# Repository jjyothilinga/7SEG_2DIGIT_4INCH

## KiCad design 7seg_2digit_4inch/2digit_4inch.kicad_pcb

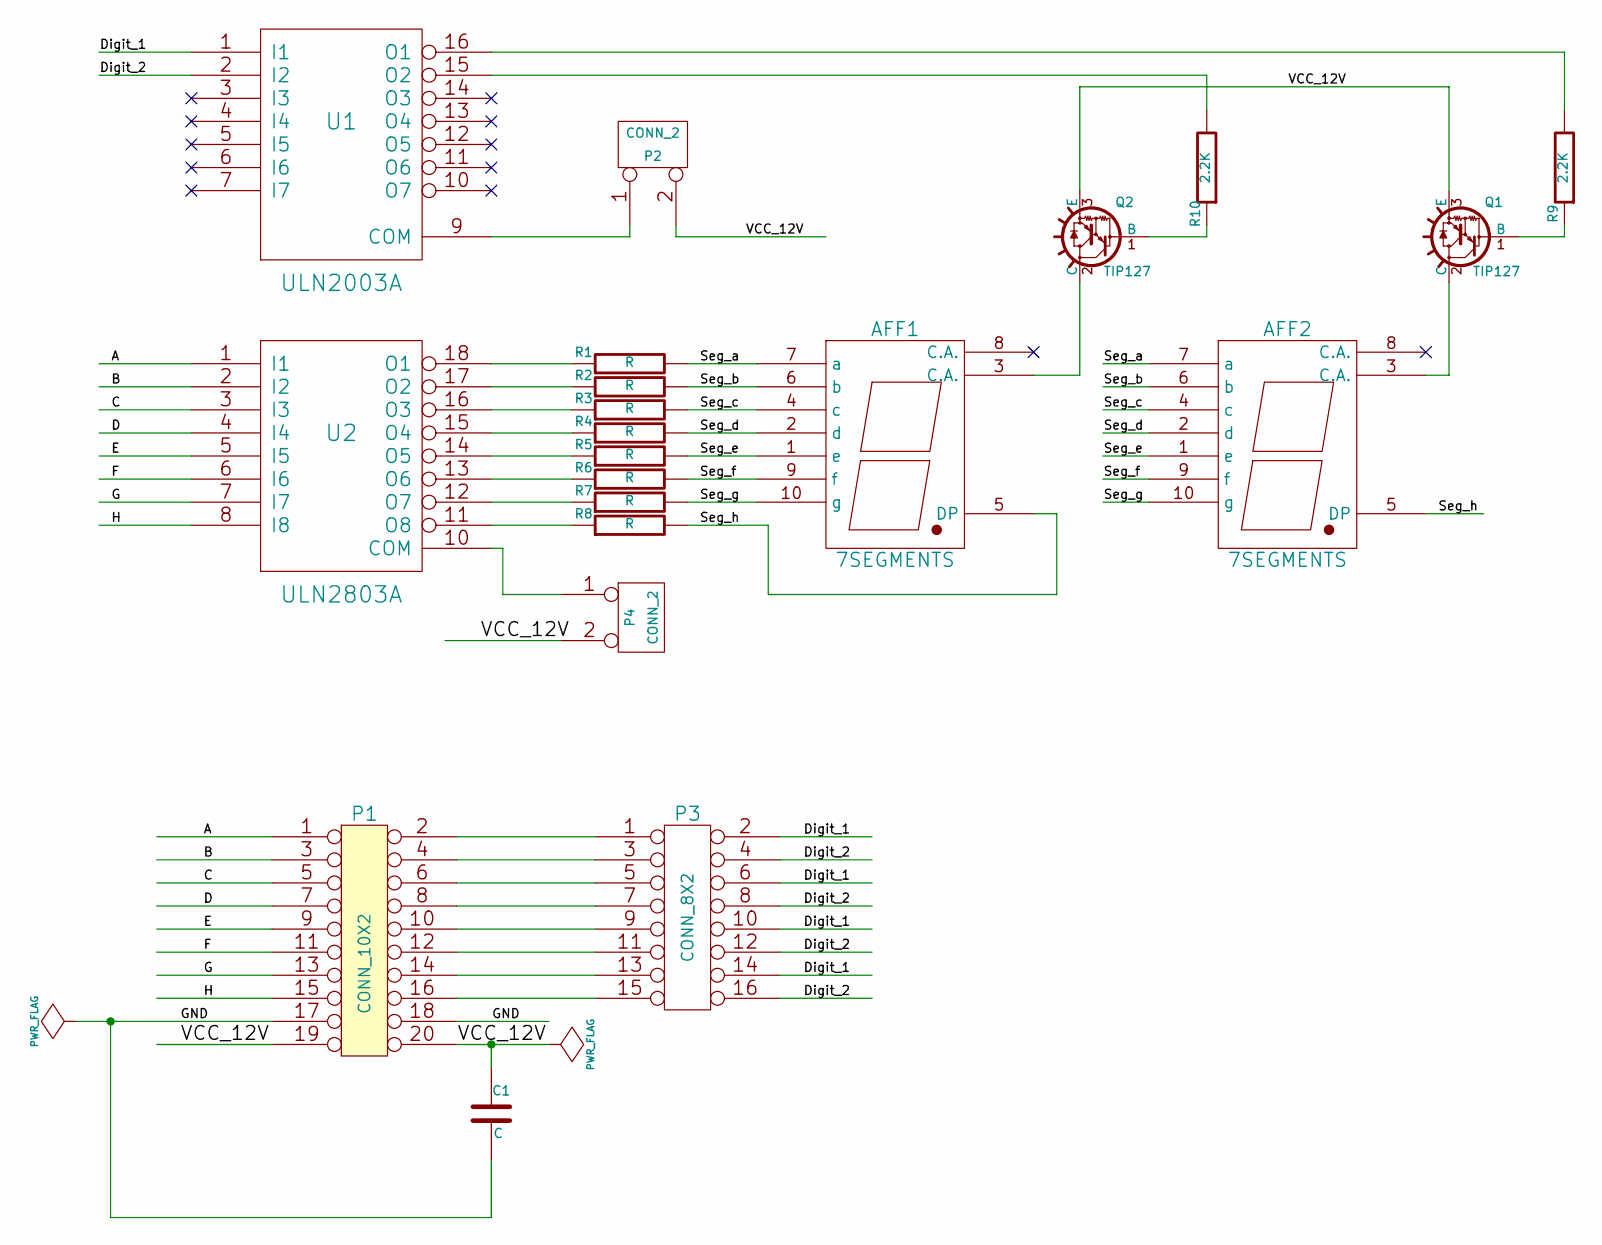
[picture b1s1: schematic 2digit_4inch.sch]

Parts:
AFF1, AFF2: 7SEGMENTS
C1: C
P1: CONN_10X2
P2, P4: CONN_2
P3: CONN_8X2
Q1, Q2: TIP127; TO220
R1, R2, R3, R4, R5, R6, R7, R8: R
R9, R10: 2.2K
U1: ULN2003A
U2: ULN2803A

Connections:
/A: P1.1, U2.1 (I1)
/B: P1.3, U2.2 (I2)
/C: P1.5, U2.3 (I3)
/D: P1.7, U2.4 (I4)
/Digit_1: P3.2, P3.6, P3.10, P3.14, U1.1 (I1)
/Digit_2: P3.4, P3.8, P3.12, P3.16, U1.2 (I2)
/E: P1.9, U2.5 (I5)
/F: P1.11, U2.6 (I6)
/G: P1.13, U2.7 (I7)
/H: P1.15, U2.8 (I8)
/Seg_a: AFF1.7 (a), AFF2.7 (a), R1.2
/Seg_b: AFF1.6 (b), AFF2.6 (b), R2.2
/Seg_c: AFF1.4 (c), AFF2.4 (c), R3.2
/Seg_d: AFF1.2 (d), AFF2.2 (d), R4.2
/Seg_e: AFF1.1 (e), AFF2.1 (e), R5.2
/Seg_f: AFF1.9 (f), AFF2.9 (f), R6.2
/Seg_g: AFF1.10 (g), AFF2.10 (g), R7.2
/Seg_h: AFF1.5 (DP), AFF2.5 (DP), R8.2
/VCC_12V: C1.1, P1.19, P1.20, P2.2 (PM), P4.2 (PM), Q1.3 (E), Q2.3 (E)
GND: C1.2, P1.17, P1.18, U1.8 (GND), U2.9 (GND)
unnamed: Q1.1 (B), R9.1
unnamed: R5.1, U2.14 (O5)
unnamed: P4.1, U2.10 (COM)
unnamed: R1.1, U2.18 (O1)
unnamed: R2.1, U2.17 (O2)
unnamed: R3.1, U2.16 (O3)
unnamed: R4.1, U2.15 (O4)
unnamed: R6.1, U2.13 (O6)
unnamed: R7.1, U2.12 (O7)
unnamed: R8.1, U2.11 (O8)
unnamed: P1.14, P3.13
unnamed: P1.12, P3.11
unnamed: P1.10, P3.9
unnamed: P1.8, P3.7
unnamed: P1.16, P3.15
unnamed: P1.6, P3.5
unnamed: P1.4, P3.3
unnamed: P1.2, P3.1
unnamed: Q2.1 (B), R10.1
unnamed: R9.2, U1.16 (O1)
unnamed: P2.1, U1.9 (COM)
unnamed: R10.2, U1.15 (O2)
unnamed: AFF2.3 (C.A.), Q1.2 (C)
unnamed: AFF1.3 (C.A.), Q2.2 (C)

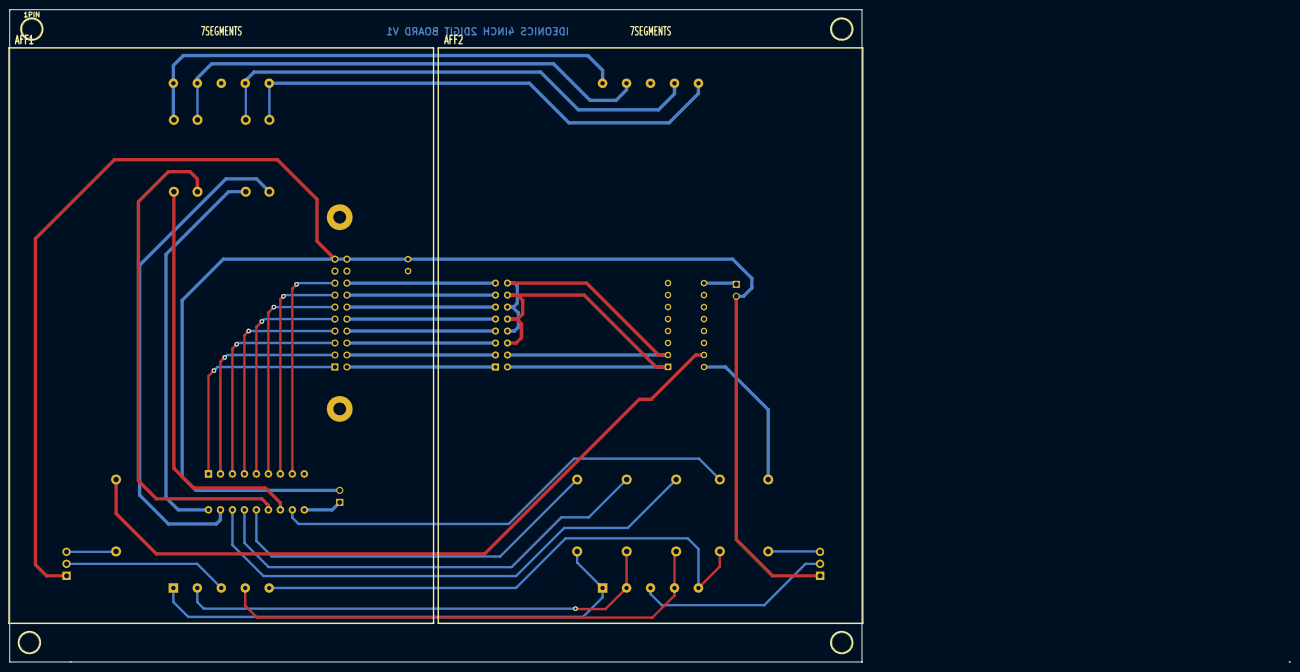
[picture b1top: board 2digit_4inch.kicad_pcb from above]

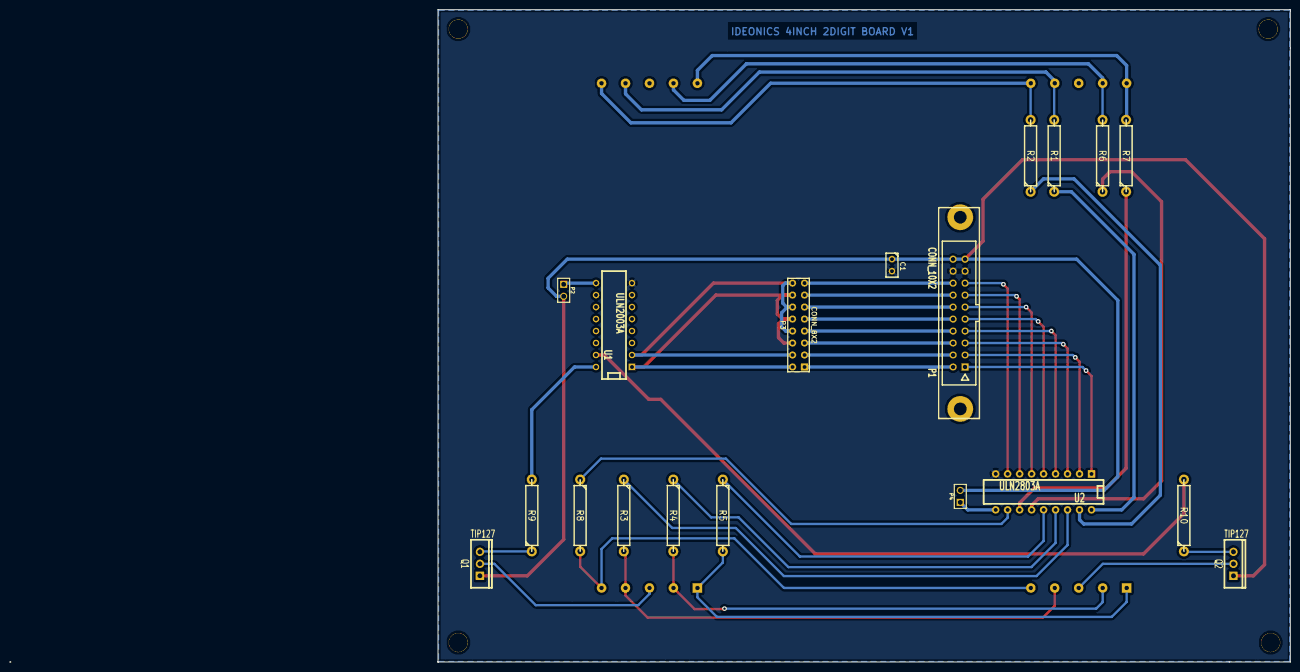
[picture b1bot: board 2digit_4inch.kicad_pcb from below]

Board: 2 copper layers, 180.7 x 138.3 mm, 25 parts (19 on the bottom side), 44 nets.

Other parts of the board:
1PIN, 1PIN#2, 1PIN#3, 1PIN#4: P***; 1pin

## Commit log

2014-12-11 :space_invader: Added .gitattributes & .gitignore files
2014-12-11 7SEG_4INCH
2015-03-13 Via dimension updated
2015-06-09 7seg_2digit_4inch added
